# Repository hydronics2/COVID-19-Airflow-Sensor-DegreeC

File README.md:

#### This sensor was abandoned because there is a 1-2 second delay in sensor-airflow output... The sensor also outputs a saw-tooth data stream... that is, it doesn't respond quickly to actual airflow volumes but slowly floats to a correct value. An ongoing airflow sensor project is here: [AFH55M12](https://github.com/hydronics2/COVID-19-Airflow-Sensor-AFH55M12) 

# Airflow - DegreeC Controls Sensor

## Project Description ([from Helpful Engineering](https://www.helpfulengineering.org/))
The intent here is to create a monitoring device, based on a mass airflow meter, that can be used when splitting a ventilator into two or more patients. This will allow staff to monitor individual patients while being controlled by one device in extreme situations where the number of ventilators are not enough to handle the number of patients. The readout should be visible locally on the device and there may need to be parameters input by staff to create a safe operating range and to possibly create alarms when the system is measuring an out of range parameter.

### [Project Requirements](https://docs.google.com/document/d/17Ps910A2vRwnM4EM6F-71GNG1XNa0PaeImd53F7428c/edit?usp=sharing)

This is a prototype using the [DegreeC controls F662-A air flow sensor](https://degree-controls-inc.myshopify.com/pages/f660-662)

Prototype board has an OLED screen and user interface rotary encoder and button.

Airflow sensor, humidity sensor and gauge pressure sensor is rear mounted.

A cavity in a tube exposes the sensors to the airstream.

### Notes:
- Using a 1” diameter tube and normal inhale of 500mL gives an average air velocity of 0.328 m/s
	- 500 ml / (1.27 cm ^2 * pi) /3 sec/ 100.

### Bill of Materials
	- DegreeC Airflow sensor [f662-A](https://degree-controls-inc.myshopify.com/pages/f660-662)
	- gauge pressure sensor, MP3V5004G [NXP MP3V5004 Series](https://www.nxp.com/docs/en/data-sheet/MP3V5004G.pdf)
	- humidity sensor through-hole - H1H800, digikey 480-5706-1-ND
	- humidity sensor surface mount - SHTC3, digikey 1649-1100-1-ND
	- piezo buzzer, generic, 6.5mm pitch
	- transistor to drive piezo pn2222A
	- oled display, generic 1306 OLED, 128 x 64 pixels
	- Linear 3.3v regulator LDL1117S33R
	- Rotary Encoder and momentary switch, Bourns PEC12R-4220F-S0012-ND
	- generic 6mm user defined momentary tactile switch
	- generic 1206 smd LEDs for Power, Error, and TBD LED indicator

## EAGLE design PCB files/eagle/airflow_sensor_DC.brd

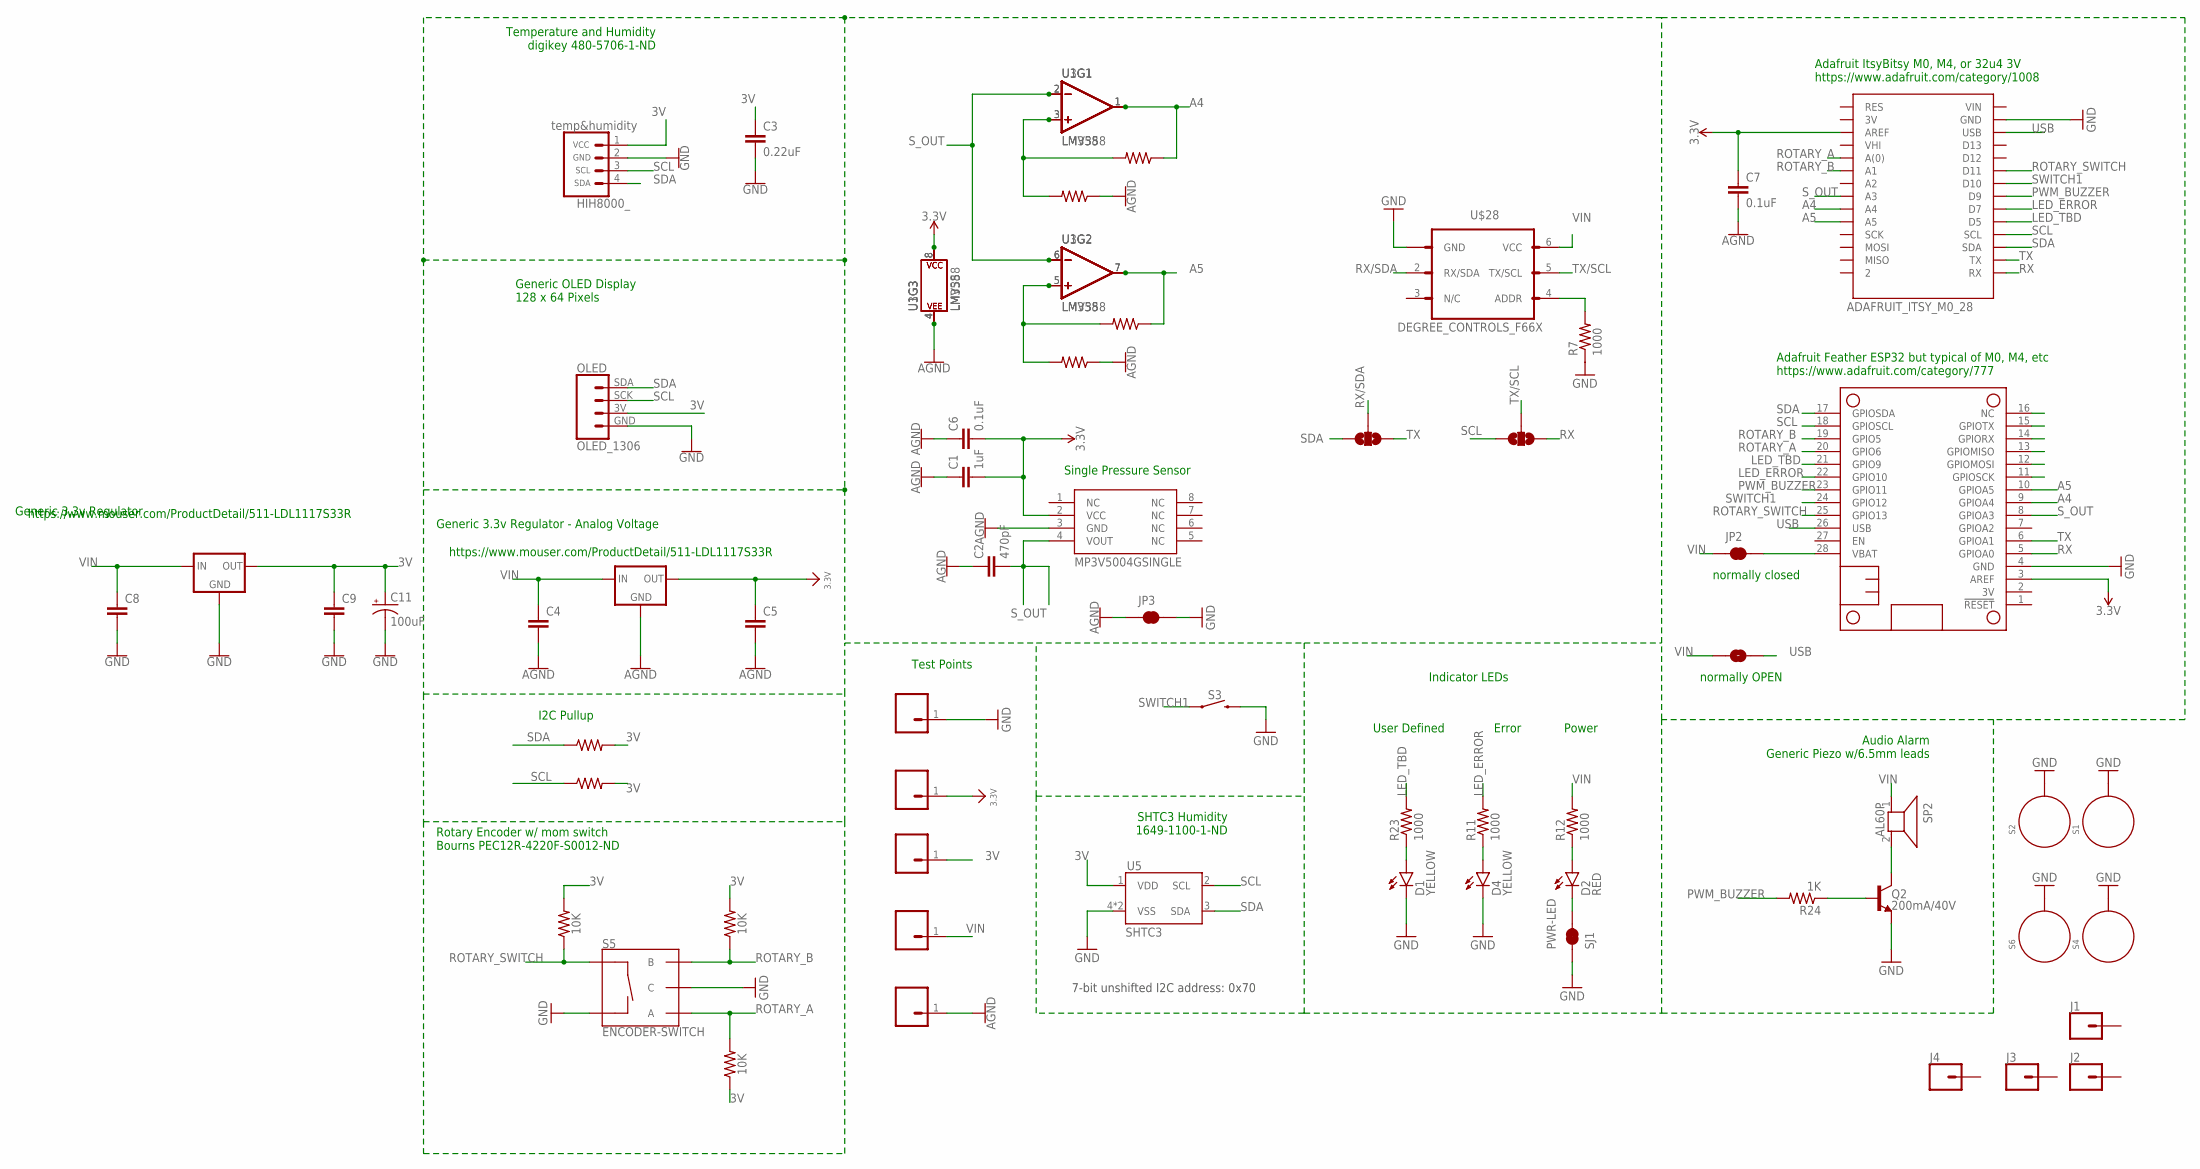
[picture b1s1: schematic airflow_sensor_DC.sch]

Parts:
3V_REGULATOR, 3V_REGULATOR1: LDL1117_5V_REG; SOT223
C1: 1uF; 0805
C2: 470pF; 0805
C3: 0.22uF; 0805
C4, C5, C8, C9: CAP-0805; 0805
C6, C7: 0.1uF; 0805
C11: 100uF; CPOL-RADIAL-2.5MM-6.5MM
D1, D4: YELLOW; LED-1206
D2: RED; LED-1206
J1, J2, J3, J4: CONN_01; 1X01
JP1: JUMPER-SMT_2_NO_NO-SILK; SMT-JUMPER_2_NO_NO-SILK
JP2, JP3: JUMPER-SMT_2_NC_TRACE_SILK; SMT-JUMPER_2_NC_TRACE_SILK
JP4, JP5: JUMPER-SMT_3_NO_NO-SILK; SMT-JUMPER_3_NO_NO-SILK
MS2: FEATHERWING_NODIM; FEATHERWING_DIM
Q2: 200mA/40V; TO-92
R3, R4, R5, R8: tbd; 0805
R7, R11, R12, R23: 1000; 0805
R21, R22: 0.3; 0805
R24: 1K; 0805
R26, R27, R28: 10K; 0805
S1, S2, S4, S6: STANDOFF_ELECTRICAL5-32; STANDOFF_ELECTRICAL_5_32
S3: MOMENTARY-SWITCH-SPST-PTH-6.0MM-KIT; TACTILE_SWITCH_PTH_6.0MM_KIT
S5: ENCODER-SWITCH; ROTARY_ENC_PLAIN
SJ1: PWR-LED; PAD-JUMPER-2-NC_BY_TRACE_NO_SILK
SP2: AL60P
U1: LM358; DIP08
U3: LMV358; SO08
U5: SHTC3
U$1: OLED_1306
U$2: MP3V5004GSINGLE; MP3V5004GP
U$4: HIH8000_; HIH8120_TH
U$20, U$26, U$31, U$39, U$40: CONN_0138MILL; 1X01-40MILL
U$28: DEGREE_CONTROLS_F66X; F660/F662
U$45: ADAFRUIT_ITSY_M0_28; ADAFRUIT_ITS_MO_28

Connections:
3.3V: 3V_REGULATOR.2 (OUT), 3V_REGULATOR.4 (OUT), C1.2, C5.1, C6.2, C7.1, MS2.3 (AREF), U1.8 (P$V+), U3.8 (P$V+), U$2.2 (VCC), U$39.1, U$45.AREF
3V: 3V_REGULATOR1.2 (OUT), 3V_REGULATOR1.4 (OUT), C3.1, C9.1, C11.1 (+), R21.2, R22.2, R26.2, R27.1, R28.2, U5.1 (VDD), U$1.3V (VCC), U$4.1 (VCC), U$20.1
A4: MS2.9 (GPIOA4), R8.1, U1.1 (OUT), U3.1 (OUT), U$45.A4
A5: MS2.10 (GPIOA5), R4.1, U1.7 (OUT), U3.7 (OUT), U$45.A5
AGND: 3V_REGULATOR.1 (GND), C1.1, C2.1, C4.2, C5.2, C6.1, C7.2, JP3.1, R3.1, R5.1, U1.4 (P$V-), U3.4 (P$V-), U$2.3 (GND), U$26.1
GND: 3V_REGULATOR1.1 (GND), C3.2, C8.2, C9.2, C11.2 (-), D1.C, D4.C, JP3.2, MS2.4 (GND), Q2.1 (E), R7.1, S1.P1, S2.P1, S3.3 (2), S4.P1, S5.C, S5.SW-, S6.P1, SJ1.1, U5.4 (VSS), U5.5 (VSS), U$1.GND, U$4.2 (GND), U$28.1 (GND), U$31.1, U$45.GND
LED_ERROR: MS2.22 (GPIO10), R11.2, U$45.D7
LED_TBD: MS2.21 (GPIO9), R23.2, U$45.D5
unnamed: R3.2, R8.2, U1.3 (+IN), U3.3 (+IN)
unnamed: D2.A, R12.1
unnamed: D1.A, R23.1
unnamed: R4.2, R5.2, U1.5 (+IN), U3.5 (+IN)
unnamed: Q2.3 (C), SP2.2
unnamed: Q2.2 (B), R24.1
unnamed: D4.A, R11.1
unnamed: D2.C, SJ1.2
unnamed: R7.2, U$28.4 (ADDR)
PWM_BUZZER: MS2.23 (GPIO11), R24.2, U$45.D9
ROTARY_A: MS2.20 (GPIO6), R27.2, S5.A, U$45.A0 (A(0))
ROTARY_B: MS2.19 (GPIO5), R26.1, S5.B, U$45.A1
ROTARY_SWITCH: MS2.25 (GPIO13), R28.1, S5.SW+, U$45.D11
RX: JP5.1, MS2.5 (GPIOA0), U$45.RX
RX/SDA: JP4.2, U$28.2 (RX/SDA)
SCL: JP5.3, MS2.18 (GPIOSCL), R22.1, U5.2 (SCL), U$1.SCK, U$4.3 (SCL), U$45.SCL
SDA: JP4.3, MS2.17 (GPIOSDA), R21.1, U5.3 (SDA), U$1.SDA, U$4.4 (SDA), U$45.SDA
SWITCH1: MS2.24 (GPIO12), S3.1, U$45.D10
S_OUT: C2.2, MS2.8 (GPIOA3), U1.2 (-IN), U1.6 (-IN), U3.2 (-IN), U3.6 (-IN), U$2.4 (VOUT), U$45.A3
TX: JP4.1, MS2.6 (GPIOA1), U$45.TX
TX/SCL: JP5.2, U$28.5 (TX/SCL)
USB: JP1.2, MS2.26 (USB), U$45.USB
VBAT: JP2.2, MS2.28 (VBAT)
VIN: 3V_REGULATOR.3 (IN), 3V_REGULATOR1.3 (IN), C4.1, C8.1, JP1.1, JP2.1, R12.2, SP2.1, U$28.6 (VCC), U$40.1

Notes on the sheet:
I2C Pullup
Single Pressure Sensor
Temperature and Humidity digikey 480-5706-1-ND
Generic OLED Display 128 x 64 Pixels
normally closed
normally OPEN
Adafruit ItsyBitsy M0, M4, or 32u4 3V https://www.adafruit.com/category/1008
Adafruit Feather ESP32 but typical of M0, M4, etc https://www.adafruit.com/category/777
Generic 3.3v Regulator - Analog Voltage
Test Points
Indicator LEDs
Power
Error
User Defined
https://www.mouser.com/ProductDetail/511-LDL1117S33R
Audio Alarm Generic Piezo w/6.5mm leads
Rotary Encoder w/ mom switch Bourns PEC12R-4220F-S0012-ND
7-bit unshifted I2C address: 0x70
SHTC3 Humidity 1649-1100-1-ND
Generic 3.3v Regulator

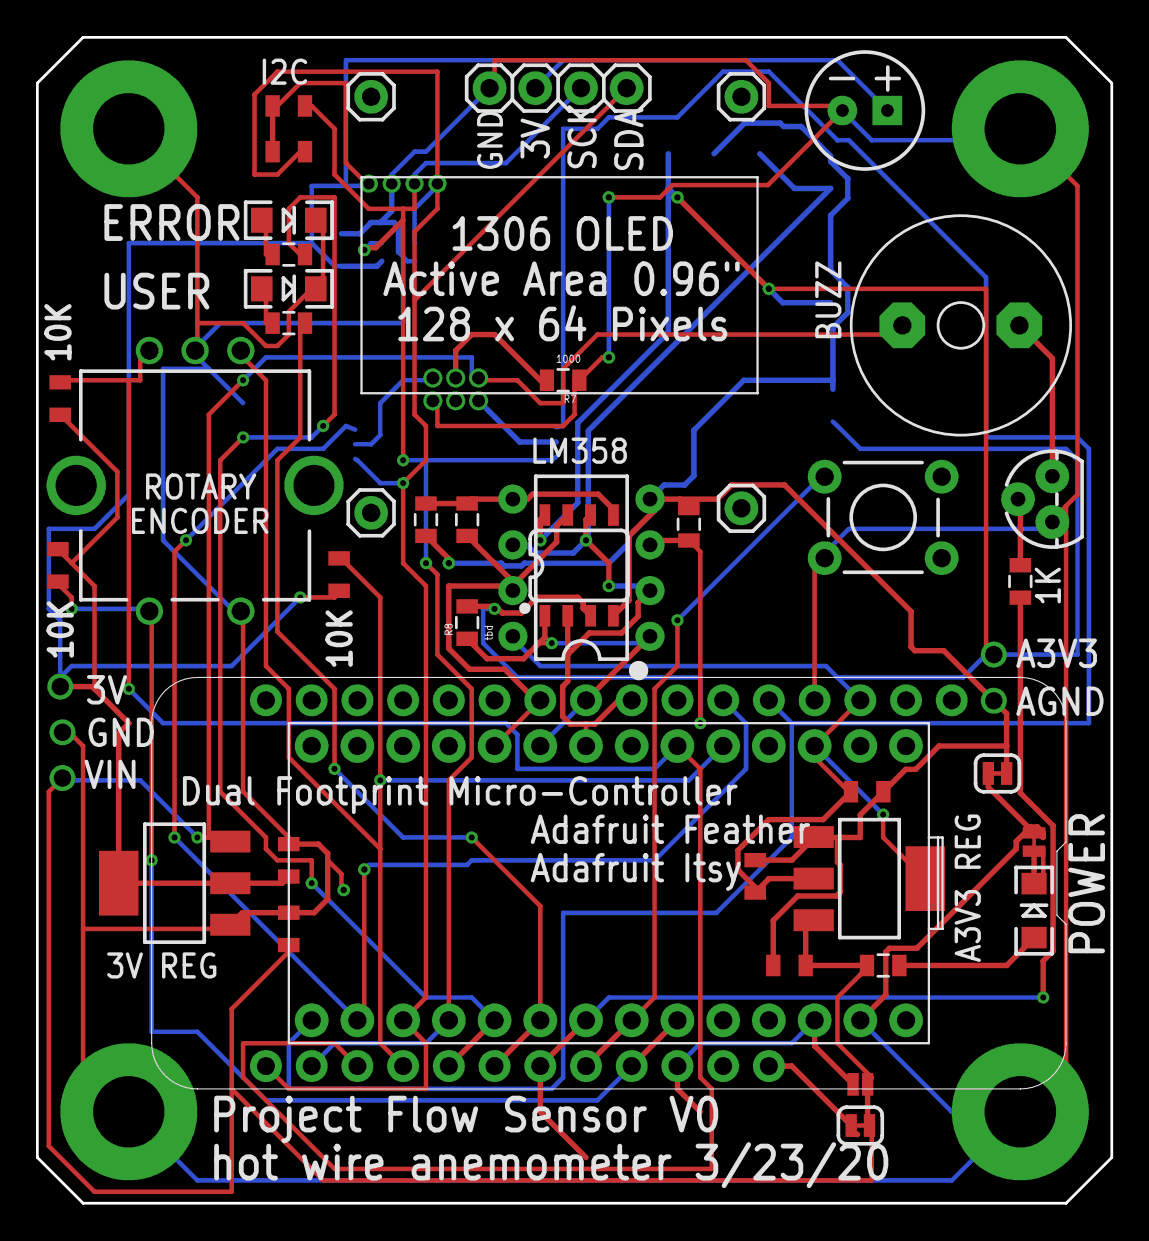
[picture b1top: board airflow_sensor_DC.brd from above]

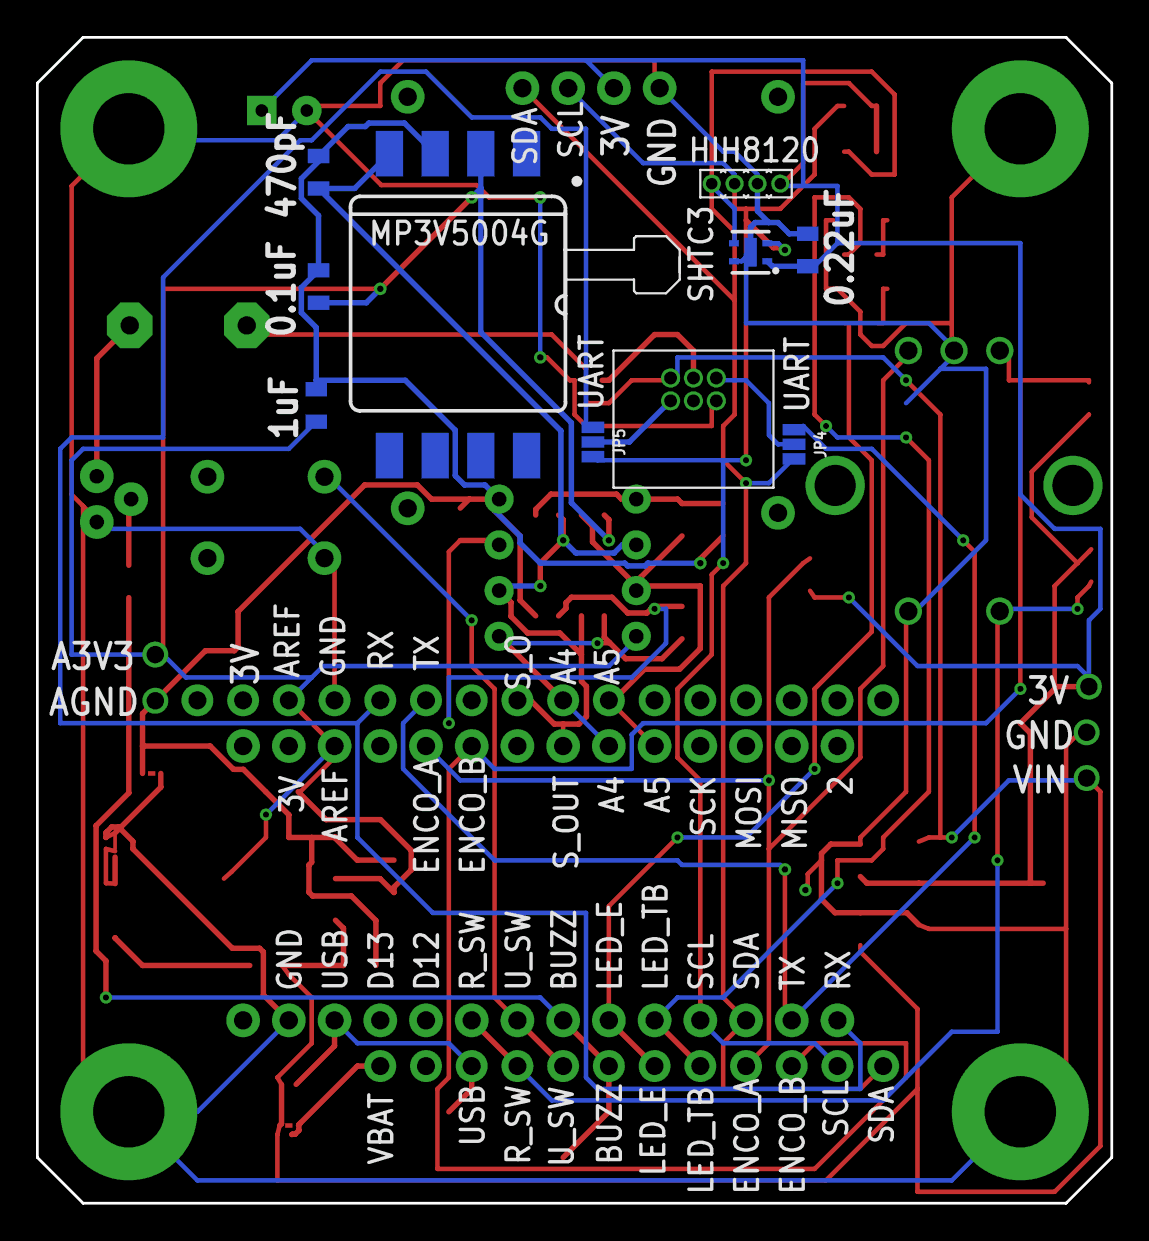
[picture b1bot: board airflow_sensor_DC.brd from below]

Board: 2 copper layers, 59.7 x 64.8 mm, 61 parts (10 on the bottom side), 32 nets.

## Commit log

2020-03-24 added pics
2020-03-24 added pcb files
2020-04-01 update notes

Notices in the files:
parts and their libraries:
SparkFun-Capacitors: Licensing: Creative Commons ShareAlike 4.0 International - https://creativecommons.org/licenses/by-sa/4.0
microbuilder: This work is placed in the public domain, and may be freely used for commercial and non-commercial work with the following conditions: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
